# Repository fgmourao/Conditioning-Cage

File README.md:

# Conditioning Cage v2.0
** Under development

Hardware, firmware and desktop interface for classical fear conditioning.  
Arduino DUE stimulus generator controlled by a Python/PyQt5 application over USB.

---

## Origin

This project is a full rewrite of the system described in:

> Amaral Junior PA, Mourao FAG, Moraes MFD (2019).  
> *A Custom Microcontrolled and Wireless-Operated Chamber for Auditory Fear Conditioning.*  
> Frontiers in Neuroscience.  
> https://doi.org/10.3389/fnins.2019.01193

The original v1.0 architecture used an ESP8266 as a Wi-Fi master communicating with the Arduino DUE via SPI, with a browser-based HTML interface. Version 2.0 removes the ESP8266 entirely — a PyQt5 desktop application communicates directly with the DUE over its native USB port.

Beyond the architectural change, v2.0 introduces several new capabilities: adaptive DAC lookup tables for lower harmonic distortion across the full frequency range, an AM modulation channel with configurable modulator frequency, two independent programmable digital trigger outputs (pins 10 and 11) for synchronising external equipment, an OLED status display, a hardware watchdog with fault detection, and a calibration interface with per-bar shock selection.

---

## Changes from v1.0 to v2.0

### Architecture
The ESP8266 Wi-Fi master and SPI bus are removed entirely. Python communicates directly with the DUE over its native USB port using newline-terminated JSON. All stimulus timing is handled autonomously by the DUE after a single `start` command — no real-time control from the host is required during execution.

### Bug fixes and stability improvements

**Shock clock decoupled from DAC** — in v1.0 the shock interval counter (`iCountShockIntervals`) was incremented inside the `carrier()` ISR, which ran at the DAC rate. Changing `carrier_freq` silently altered shock pulse timing. In v2.0 the shock has its own dedicated Timer6 running at a fixed 10 kHz, completely independent of the DAC.

**Hardware ABORT pin pullup** — in v1.0 `pinABORT` was configured as `INPUT` with no pullup resistor, leaving the pin floating when the button was not pressed and susceptible to spurious aborts from electrical noise. In v2.0 it uses `INPUT_PULLUP`.

**DAC disabled between sounds** — in v1.0 `analogWrite(DAC1, 0)` at sound offset wrote zero but left the DAC channel enabled, injecting DC noise into the amplifier between trials. In v2.0 `dacc_disable_channel` is called at every sound offset and the coupling capacitor is pre-charged to midscale before each onset to eliminate transients.

**Shock pulse timing precision** — in v1.0 `floor()` was used to convert pulse times to tick counts, introducing a systematic downward truncation error. In v2.0 `roundf()` gives the nearest tick (0.1 ms resolution at 10 kHz).

**Watchdog** — v1.0 had no hardware fault detection. If Timer4 or Timer6 stalled, the experiment continued silently with no stimuli. In v2.0 a software watchdog monitors both timers; if either stops incrementing for 5 seconds a fault is declared, all outputs are driven LOW, and the Python interface displays a critical alert.

**DAC buffer type** — in v1.0 the DAC buffer was `uint32_t` (4 bytes per sample), wasting twice the RAM needed. In v2.0 it is `uint16_t` (2 bytes per sample), halving the buffer footprint to 2 KB.

### Sound generation

In v1.0 the carrier lookup table had a fixed 8 samples regardless of frequency. At low carrier frequencies (1–3 kHz) this produced visible harmonic distortion — only 8 points approximated each sine cycle. In v2.0 adaptive tables select 4, 8, 16, or 32 samples based on the carrier frequency, keeping the DAC update rate within the optimal range across the full 0–20 kHz span.

### New stimuli and features

- **LIGHT** — independent light stimulus (pin 45, square wave or DC HIGH) with its own onset, duration, and frequency per trial
- **Trigger 1 / Trigger 2** — two independent digital pulse outputs (pins 10 and 11) for synchronising external equipment, with configurable onset (s) and duration (ms) per trial
- **Baseline period** — quiet time before the first trial, separate from the inter-trial interval
- **Per-trial volume control** — sound amplitude programmable per trial (0–100%)
- **AM modulation** — configurable modulator frequency per trial; `modulator_freq = 0` gives a pure sine
- **OLED status display** — real-time trial state on an SSD1306 128×32 display
- **Bar selection** — calibration mode allows fixing a single shock bar for individual verification
- **Python desktop interface** — replaces the ESP8266 HTML page with a PyQt5 application featuring a trial timeline preview, protocol save/load, event log, and calibration dialogs

---

## Architecture

```
Python / PyQt5  (PC)
      │
      │  SerialUSB — native USB port (USB CDC)
      │
Arduino DUE
      ├─ DAC1         →  Sound  (AM sine, 0–20 kHz)
      ├─ Timer4/5     →  DAC clock / AM modulator ISR
      ├─ Timer6       →  Shock clock (10 kHz)
      ├─ Timer7       →  Light square wave
      ├─ Pins 23–37   →  Shock bars (8 outputs, round-robin)
      ├─ Pin 45       →  Light output
      ├─ Pin 46       →  Watchdog fault output
      ├─ Pin 48       →  Hardware ABORT input
      ├─ Pin 10        →  Trigger 1 output (digital pulse)
      ├─ Pin 11        →  Trigger 2 output (digital pulse)
      ├─ Pins 50–53   →  Sync outputs (SOUND, LIGHT, SHOCK, MOD)
      └─ Pins 20–21   →  I²C — OLED display (SDA / SCL)
```

The DUE stores the complete trial list in RAM and executes the experiment autonomously after a single `start` command. Python is responsible only for programming parameters, triggering execution, and monitoring status.

---

## Stimuli

Five independent stimuli with individual onset and duration per trial:

### Sound
- Output: DAC1 (12-bit, 0–3.3 V)
- Waveform: AM-modulated sine (`SINE_AM`) or pure sine
- Carrier: 0–20 kHz; modulator: 0–500 Hz
- Adaptive lookup tables (see [Sound generation](#sound-generation))
- AC coupling capacitor (10 µF) recommended in series on DAC1 output

### Light
- Output: pin 45, square wave 50% duty cycle
- Frequency: configurable; `light_freq = 9999` = DC HIGH (constant ON)

### Shock
- Outputs: pins 23, 25, 27, 29, 31, 33, 35, 37 (8 bars)
- Round-robin activation or fixed single bar (calibration)
- Pulse HIGH and LOW times configurable in ms (0.1 ms resolution at 10 kHz clock)

### Trigger 1 / Trigger 2
- Outputs: pin 10 (Trigger 1), pin 11 (Trigger 2)
- Simple digital HIGH pulse: onset in seconds, duration in milliseconds
- Independent of each other and of all other stimuli
- Intended for synchronising external equipment (cameras, stimulators, recording systems)

---

## Trial structure

Each trial stores 20 float parameters, transmitted semicolon-separated over serial:

| Field | Description | Unit |
|---|---|---|
| `baseline` | Quiet period before first trial | s |
| `silence` | Inter-trial interval | s |
| `onset_sound` | Sound onset within trial | s |
| `sound_duration` | Sound duration | s |
| `carrier_freq` | DAC carrier frequency; 0 = no sound | Hz |
| `modulator_freq` | AM modulator frequency; 0 = pure sine | Hz |
| `volume` | Sound amplitude | % |
| `waveform_type` | 0 = SINE_AM, 1 = SINE, 2 = SQUARE | — |
| `onset_shock` | Shock onset within trial | s |
| `shock_duration` | Shock duration; 0 = no shock | s |
| `pulse_high` | Shock bar ON time per pulse | ms |
| `pulse_low` | Shock bar OFF time between pulses | ms |
| `onset_light` | Light onset within trial | s |
| `light_duration` | Light duration; 0 = no light | s |
| `light_freq` | Light frequency; 9999 = DC HIGH | Hz |
| `bar_select` | 0 = round-robin, 1–8 = fixed bar | — |
| `onset_trig1` | Trigger 1 onset within trial; 0 = start of trial | s |
| `trig1_duration` | Trigger 1 pulse duration; 0 = disabled | ms |
| `onset_trig2` | Trigger 2 onset within trial; 0 = start of trial | s |
| `trig2_duration` | Trigger 2 pulse duration; 0 = disabled | ms |

---

## Serial protocol

All communication uses newline-terminated JSON objects:

```
{"cmd":"ping"}
    -> {"ok":true,"msg":"pong","version":"2.0"}

{"cmd":"program","n":N,"data":"f0;f1;..."}
    -> {"ok":true,"msg":"N trials programmed"}

{"cmd":"start"}
    -> {"ok":true,"msg":"started"}

{"cmd":"abort"}
    -> {"ok":true,"msg":"aborted"}

{"cmd":"status"}
    -> {"ok":true,"status":N,"trial":N,"total":N,
        "running":bool,"ready":bool,"fault":bool}
```

Status codes: `0` IDLE · `1` READY · `2` RUNNING · `3` DONE · `4` FAULT · `5` ABORTED

---

## Sync outputs

All sync pins are active HIGH while the corresponding stimulus is active.  
**Use these pins as the authoritative timing reference for external equipment** (electrophysiology, cameras). The `onset_*` fields in seconds carry a worst-case jitter of ~500 µs (one loop iteration); the sync pins do not.

| Pin | Signal | Description |
|---|---|---|
| 50 | SOUND_SYN | HIGH while sound is playing |
| 51 | LIGHT_SYN | HIGH while light is active |
| 52 | SHOCK_SYN | HIGH while shock is being delivered |
| 53 | MOD_SYN | Square wave at `modulator_freq`, phase-locked to AM envelope |

---

## OLED status display

Optional SSD1306 128×32 OLED on I²C (SDA = pin 20, SCL = pin 21, address 0x3C).  
Shows experiment state at each transition:

| State | Display |
|---|---|
| Startup | `Conditioning Cage / v2.0 Ready` |
| Trial onset | `TRIAL X/N` / `CS` · `CS + US` · `US` |
| Done | `Conditioning Cage / Done` |
| Aborted | `Conditioning Cage / Aborted` |

The firmware runs normally if the display is not connected.

---

## Sound generation

v2.0 uses adaptive lookup tables (`Waveforms.h`) to minimise harmonic distortion across the full frequency range:

| Carrier frequency | Table size | DAC update rate |
|---|---|---|
| > 10 000 Hz | 4 samples | up to 80 kHz |
| > 3 000 Hz | 8 samples | up to 80 kHz |
| > 1 000 Hz | 16 samples | up to 48 kHz |
| ≤ 1 000 Hz | 32 samples | up to 32 kHz |

All rates are within the SAM3X8E DAC hardware limit of 1 MHz.  
Buffer RAM cost: 32 × 32 × 2 bytes = 2 KB.

AM modulation uses a 32-sample unipolar envelope table. When `modulator_freq = 0` the carrier is output as a pure sine with no modulation.

---

## DAC signal conditioning

The DAC1 output is 0–3.3 V (unipolar). For audio output:

- Place a **10 µF electrolytic capacitor** in series (positive pole toward DAC1) to block DC and pass the AC signal
- Place a **10 kΩ resistor** between the amplifier input and GND to anchor the input when the DAC is disabled
- Use a **potentiometer (10–50 kΩ)** between the capacitor and the amplifier input for level control
- Connect the cable shield to GND on the DUE side only (single-end grounding prevents ground loops)

The firmware disables DAC1 between sounds (`dacc_disable_channel`) and pre-charges the coupling capacitor to midscale before each trial onset to prevent transients.

---

## Python application

### Requirements

```
pip install pyserial PyQt5
```

Python 3.8 or later.

### Features

- Dark/Light-theme PyQt5 desktop application
- Trial configuration panel: per-stimulus onset, duration, frequency, volume, pulse timing, trigger durations
- Recorded trials table with per-row delete
- Timeline preview: block diagram of all trials on a shared time axis with a real-time progress line during execution; rows are shown only for stimuli with non-zero duration
- Event log with timestamps (`YYYY-MM-DD HH:MM:SS`) — exportable via Save Log
- **Protocol menu:** Save Protocol, Load Protocol, Clear All Trials, Save Log
- **Calibration menu:** Sound, Light, Shock — continuous single-trial stimulus stopped by ABORT; shock calibration allows bar selection and configurable pulse timing
- **Help menu:** Info dialog
- Port selector with refresh button
- 4-second timeout warning if DUE does not respond after connection
- Firmware version check on connect (warns if not v2.0)
- Watchdog fault popup with critical alert
- Hardware ABORT button (pin 48) is read inside the trial timing loop and during inter-trial silences — responsive at any point during experiment execution

### Poll strategy

The poll timer (`{"cmd":"status"}` every 1500 ms) is stopped when the experiment starts to prevent USB interrupt collisions with Timer4 on the Native Port. One poll is scheduled at the calculated onset of each trial using `QTimer.singleShot`. A generation counter invalidates scheduled polls that remain pending after an ABORT. The poll timer resumes when the experiment ends or is aborted.

---

## Hardware requirements

| Component | Specification |
|---|---|
| Microcontroller | Arduino DUE |
| USB connection | Native port (second USB connector) |
| Shock bars | 8 outputs — pins 23, 25, 27, 29, 31, 33, 35, 37 |
| Light output | Pin 45 |
| Trigger 1 output | Pin 10 — digital pulse |
| Trigger 2 output | Pin 11 — digital pulse |
| ABORT button | Momentary switch — pin 48 to GND |
| DAC coupling | 10 µF electrolytic capacitor in series on DAC1 |
| Amplifier | Class-D module (e.g. TDA8932); 10–50 kΩ potentiometer at input |
| Speaker | Tweeter (2–20 kHz); 4 Ω or 8 Ω |
| OLED (optional) | SSD1306 128×32, I²C, address 0x3C |

---

## Files

| File | Description |
|---|---|
| `cage_app_dark.py` | Main application — dark theme |
| `Stimuli_PY_DUE.ino` | Arduino DUE firmware |
| `Waveforms.h` | Adaptive DAC lookup tables |
| `image.png` | Logo displayed in the application header |

Arduino library dependencies (install via Arduino IDE Library Manager):
- **DueTimer** (Ivan Seidel)
- **Adafruit GFX Library**
- **Adafruit SSD1306**

---

## Known limitations

- Noise waveforms (white, pink) are not implemented. The lookup-table architecture is periodic; a possible approach is to generate noise buffers in Python (NumPy/SciPy) and send them as custom tables over serial.
- If the USB cable is disconnected during an experiment, the DUE continues executing autonomously. The only way to stop it is the hardware ABORT button (pin 48).

---

## License

Documentation licensed under Creative Commons Attribution-NonCommercial 4.0 International (CC BY-NC 4.0).

---

## Authors

**v1.0 (2019)**  
Paulo Aparecido Amaral Junior, Flavio Afonso Goncalves Mourao, Marcio Flavio Dutra Moraes  
*Núcleo de Neurociências, Federal University of Minas Gerais, Brazil*

**v2.0 (2026)**  
Flavio Afonso Goncalves Mourao — [mourao.fg@gmail.com](mailto:mourao.fg@gmail.com)  
*CNPq/MCTI/FNDCT Nº 21/2024 — Processo 446467/2024-3*  
*Federal University of Minas Gerais, Brazil*

---

*Last update: April 2026*

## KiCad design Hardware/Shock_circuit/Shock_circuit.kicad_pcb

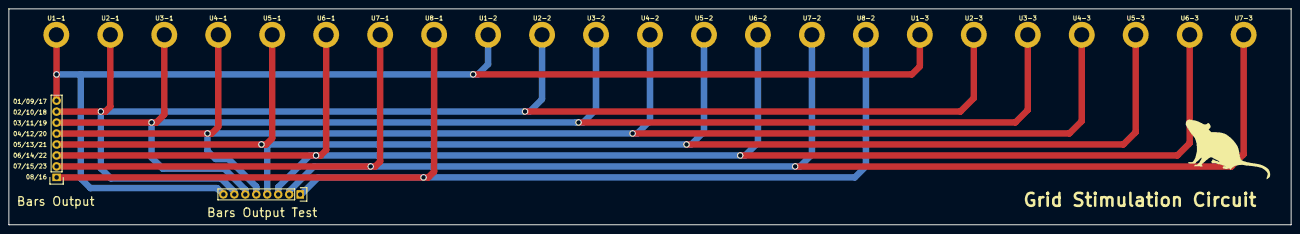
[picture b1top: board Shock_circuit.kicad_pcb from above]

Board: 2 copper layers, 297.0 x 50.0 mm, 25 parts (0 on the bottom side), 8 nets.

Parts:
P1: Bars Output Test; Pin_Header_Straight_1x08
P2: Bars Output; Pin_Header_Straight_1x08
U1-1, U1-2, U1-3, U2-1, U2-2, U2-3, U3-1, U3-2, U3-3, U4-1, U4-2, U4-3, U5-1, U5-2, U5-3, U6-1, U6-2, U6-3, U7-1, U7-2, U7-3, U8-1, U8-2: Bar_Hole

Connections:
/InBarra1: P1.8, P2.8, U1-1.1, U1-2.1, U1-3.1
/InBarra2: P1.7, P2.7, U2-1.1, U2-2.1, U2-3.1
/InBarra3: P1.6, P2.6, U3-1.1, U3-2.1, U3-3.1
/InBarra4: P1.5, P2.5, U4-1.1, U4-2.1, U4-3.1
/InBarra5: P1.4, P2.4, U5-1.1, U5-2.1, U5-3.1
/InBarra6: P1.3, P2.3, U6-1.1, U6-2.1, U6-3.1
/InBarra7: P1.2, P2.2, U7-1.1, U7-2.1, U7-3.1
/InBarra8: P1.1, P2.1, U8-1.1, U8-2.1

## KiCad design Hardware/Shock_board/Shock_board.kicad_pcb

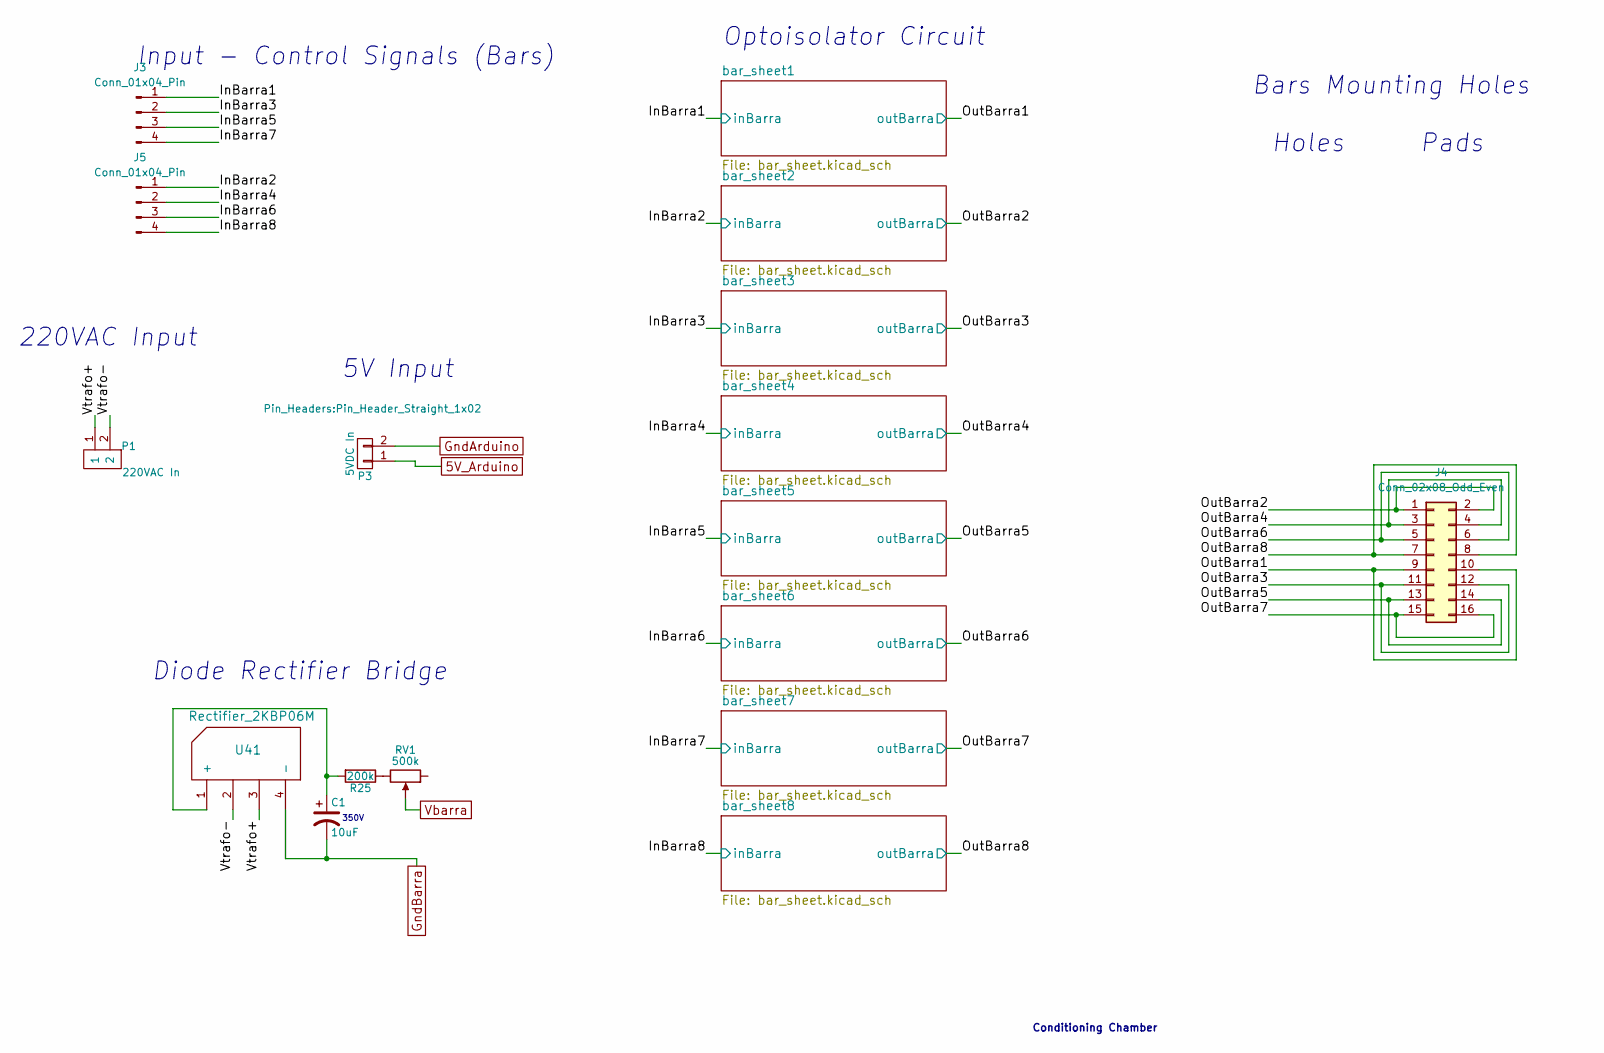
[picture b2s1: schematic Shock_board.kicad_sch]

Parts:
C1: 10uF; CP_Radial_D10.0mm_P7.50mm
J3: Conn_01x04_Pin; PinHeader_1x04_P2.54mm_Vertical
J4: Conn_02x08_Odd_Even; IDC-Header_2x08_P2.54mm_Vertical
J5: Conn_01x04_Pin; PinSocket_1x04_P2.54mm_Vertical
P1: 220VAC In; Pin_Header_Straight_1x02_Pitch2.54mm
P3: 5VDC In; Pin_Header_Straight_1x02
R25: 200k; R_Axial_DIN0207_L6.3mm_D2.5mm_P10.16mm_Horizontal
RV1: 500k; Potentiometer_Alps_RK163_Single_Vertical
U41: Rectifier_2KBP06M

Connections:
5V_Arduino: P3.1; also elsewhere on the board
/Vtrafo+: P1.1, U41.3
/Vtrafo-: P1.2, U41.2
GndArduino: P3.2; also elsewhere on the board
GndBarra: C1.2, U41.4 (-); also elsewhere on the board
unnamed: J4.1, J4.2
unnamed: J4.3, J4.4
unnamed: J4.5, J4.6
unnamed: J4.7, J4.8
unnamed: J4.9, J4.10
unnamed: J4.11, J4.12
unnamed: J4.13, J4.14
unnamed: J4.15, J4.16
unnamed 53: R25.1, RV1.3; also elsewhere on the board
unnamed: C1.1, R25.2, U41.1 (+)

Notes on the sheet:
350V
Input - Control Signals (Bars)
Diode Rectifier Bridge
220VAC Input
Bars Mounting Holes
Optoisolator Circuit
5V Input
Holes
Conditioning Chamber
Pads

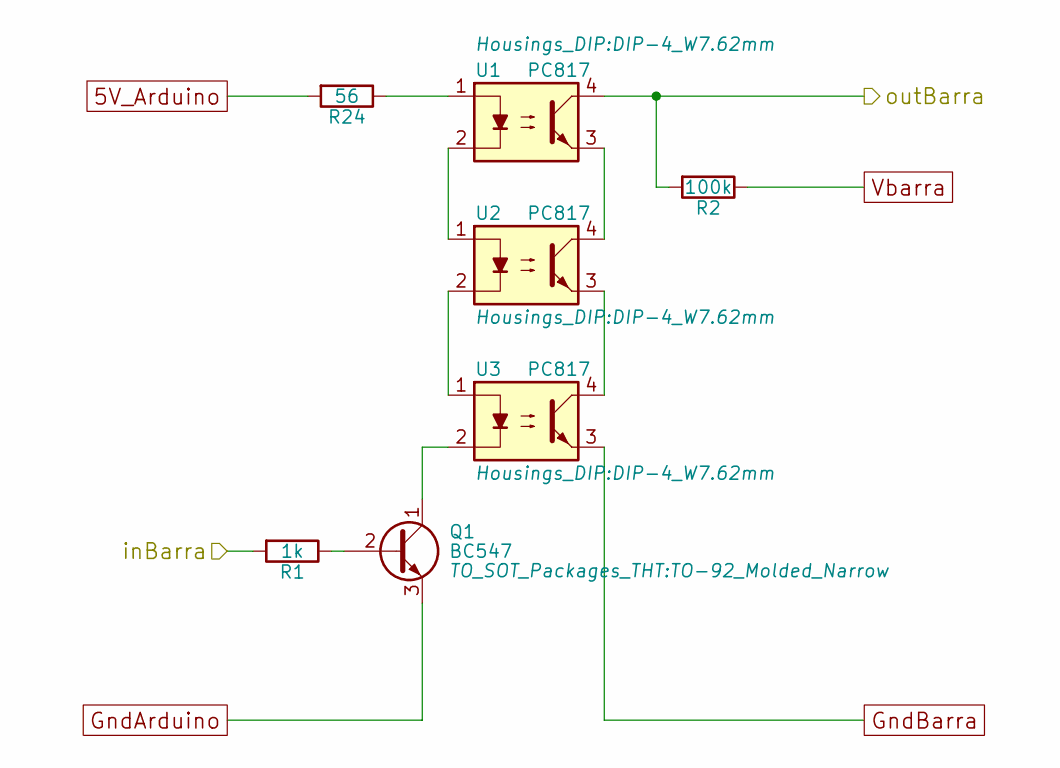
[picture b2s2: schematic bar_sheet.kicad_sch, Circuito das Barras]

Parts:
Q1: BC547; TO-92_Molded_Narrow
R1: 1k; R_Axial_DIN0207_L6.3mm_D2.5mm_P10.16mm_Horizontal
R2: 100k; R_Axial_DIN0411_L9.9mm_D3.6mm_P5.08mm_Vertical
R24: 56; R_Axial_DIN0207_L6.3mm_D2.5mm_P10.16mm_Horizontal
U1, U2, U3: PC817; DIP-4_W7.62mm

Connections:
5V_Arduino: R24.2; also elsewhere on the board
/InBarra1: R1.2; also elsewhere on the board
/OutBarra1: R2.2, U1.4; also elsewhere on the board
GndArduino: Q1.3 (E); also elsewhere on the board
GndBarra: U3.3; also elsewhere on the board
unnamed: Q1.2 (B), R1.1
unnamed: Q1.1 (C), U3.2
unnamed: R24.1, U1.1
unnamed: U1.2, U2.1
unnamed: U1.3, U2.4
unnamed: U2.2, U3.1
unnamed: U2.3, U3.4
Vbarra: R2.1; also elsewhere on the board

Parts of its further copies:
Q2, Q3, Q4, Q5, Q6, Q7, Q8: BC547; TO-92_Molded_Narrow
R3, R5, R7, R9, R11, R13, R15: 1k; R_Axial_DIN0207_L6.3mm_D2.5mm_P10.16mm_Horizontal
R4, R6, R8, R10, R12, R14, R16: 100k; R_Axial_DIN0411_L9.9mm_D3.6mm_P5.08mm_Vertical
R17, R18, R19, R20, R21, R22, R23: 56; R_Axial_DIN0207_L6.3mm_D2.5mm_P10.16mm_Horizontal
U4, U5, U6, U7, U8, U9, U10, U11, U12, U13, U14, U15, U16, U17, U18, U19, U20, U21, U22, U23, U24: PC817; DIP-4_W7.62mm

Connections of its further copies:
5V_Arduino: R17.2, R18.2, R19.2, R20.2, R21.2, R22.2, R23.2; also elsewhere on the board
/InBarra2: R3.2; also elsewhere on the board
/InBarra3: R5.2; also elsewhere on the board
/InBarra4: R7.2; also elsewhere on the board
/InBarra5: R9.2; also elsewhere on the board
/InBarra6: R11.2; also elsewhere on the board
/InBarra7: R13.2; also elsewhere on the board
/InBarra8: R15.2; also elsewhere on the board
/OutBarra2: R4.2, U4.4; also elsewhere on the board
/OutBarra3: R6.2, U7.4; also elsewhere on the board
/OutBarra4: R8.2, U10.4; also elsewhere on the board
/OutBarra5: R10.2, U13.4; also elsewhere on the board
/OutBarra6: R12.2, U16.4; also elsewhere on the board
/OutBarra7: R14.2, U19.4; also elsewhere on the board
/OutBarra8: R16.2, U22.4; also elsewhere on the board
GndArduino: Q2.3 (E), Q3.3 (E), Q4.3 (E), Q5.3 (E), Q6.3 (E), Q7.3 (E), Q8.3 (E); also elsewhere on the board
GndBarra: U6.3, U9.3, U12.3, U15.3, U18.3, U21.3, U24.3; also elsewhere on the board
unnamed: Q2.2 (B), R3.1
unnamed: Q2.1 (C), U6.2
unnamed: Q3.2 (B), R5.1
unnamed: Q3.1 (C), U9.2
unnamed: Q4.2 (B), R7.1
unnamed: Q4.1 (C), U12.2
unnamed: Q5.2 (B), R9.1
unnamed: Q5.1 (C), U15.2
unnamed: Q6.2 (B), R11.1
unnamed: Q6.1 (C), U18.2
unnamed: Q7.2 (B), R13.1
unnamed: Q7.1 (C), U21.2
unnamed: Q8.2 (B), R15.1
unnamed: Q8.1 (C), U24.2
unnamed: R17.1, U7.1
unnamed: R18.1, U10.1
unnamed: R19.1, U13.1
unnamed: R20.1, U16.1
unnamed: R21.1, U19.1
unnamed: R22.1, U22.1
unnamed: R23.1, U4.1
unnamed: U4.2, U5.1
unnamed: U4.3, U5.4
unnamed: U5.2, U6.1
unnamed: U5.3, U6.4
unnamed: U7.2, U8.1
unnamed: U7.3, U8.4
unnamed: U8.2, U9.1
unnamed: U8.3, U9.4
unnamed: U10.2, U11.1
unnamed: U10.3, U11.4
unnamed: U11.2, U12.1
unnamed: U11.3, U12.4
unnamed: U13.2, U14.1
unnamed: U13.3, U14.4
unnamed: U14.2, U15.1
unnamed: U14.3, U15.4
unnamed: U16.2, U17.1
unnamed: U16.3, U17.4
unnamed: U17.2, U18.1
unnamed: U17.3, U18.4
unnamed: U19.2, U20.1
unnamed: U19.3, U20.4
unnamed: U20.2, U21.1
unnamed: U20.3, U21.4
unnamed: U22.2, U23.1
unnamed: U22.3, U23.4
unnamed: U23.2, U24.1
unnamed: U23.3, U24.4
Vbarra: R4.1, R6.1, R8.1, R10.1, R12.1, R14.1, R16.1; also elsewhere on the board

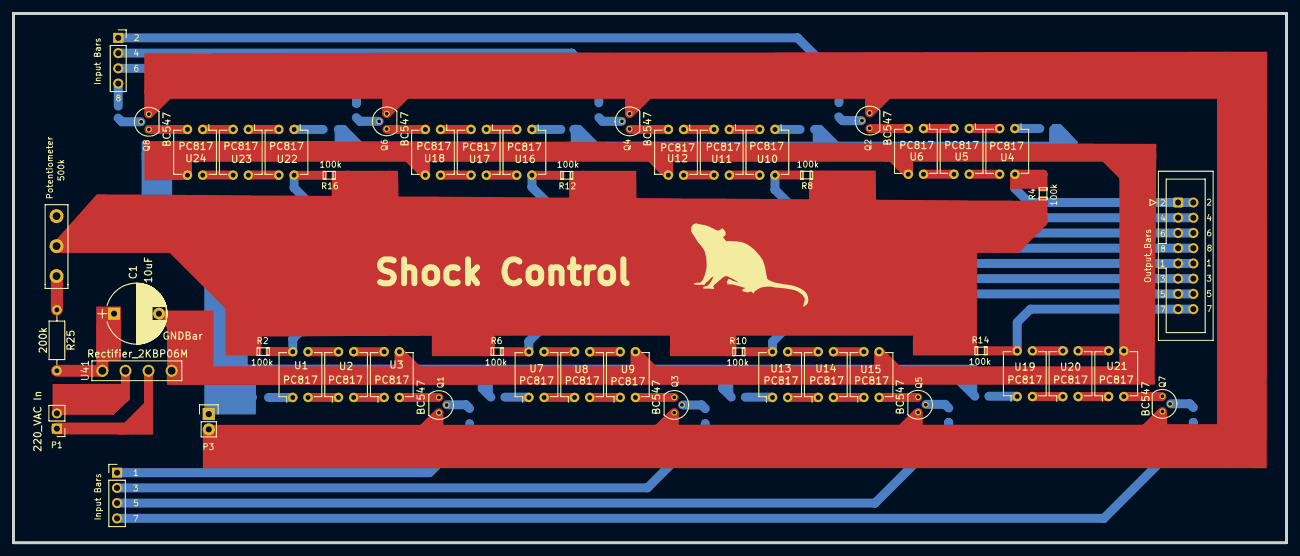
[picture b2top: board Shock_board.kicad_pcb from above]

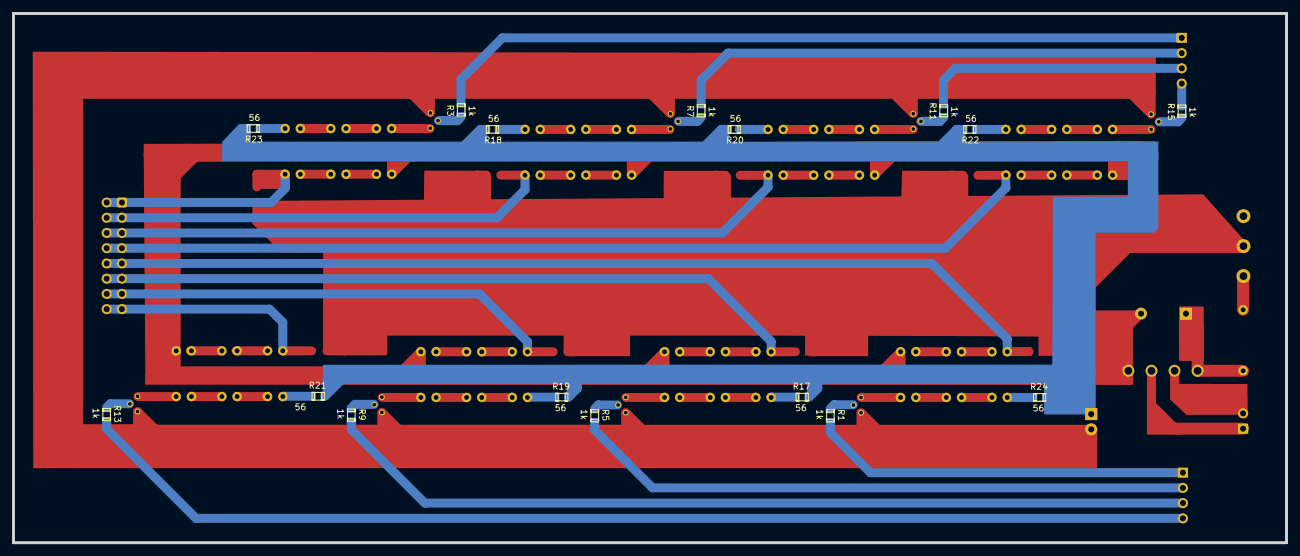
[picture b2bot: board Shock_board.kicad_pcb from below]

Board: 2 copper layers, 212.3 x 88.3 mm, 65 parts (16 on the bottom side), 80 nets.

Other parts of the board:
Input Bars: PinHeader_1x04_P2.54mm_Vertical
Input Bars#2: PinSocket_1x04_P2.54mm_Vertical
Output_Bars: IDC-Header_2x08_P2.54mm_Vertical
Potentiometer: 500k; Potentiometer_Alps_RK163_Single_Vertical

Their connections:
/InBarra1: Input Bars.1; also elsewhere on the board
/InBarra2: Input Bars#2.1; also elsewhere on the board
/InBarra3: Input Bars.2; also elsewhere on the board
/InBarra4: Input Bars#2.2; also elsewhere on the board
/InBarra5: Input Bars.3; also elsewhere on the board
/InBarra6: Input Bars#2.3; also elsewhere on the board
/InBarra7: Input Bars.4; also elsewhere on the board
/InBarra8: Input Bars#2.4; also elsewhere on the board
/OutBarra1: Output_Bars.9, Output_Bars.10; also elsewhere on the board
/OutBarra2: Output_Bars.1, Output_Bars.2; also elsewhere on the board
/OutBarra3: Output_Bars.11, Output_Bars.12; also elsewhere on the board
/OutBarra4: Output_Bars.3, Output_Bars.4; also elsewhere on the board
/OutBarra5: Output_Bars.13, Output_Bars.14; also elsewhere on the board
/OutBarra6: Output_Bars.5, Output_Bars.6; also elsewhere on the board
/OutBarra7: Output_Bars.15, Output_Bars.16; also elsewhere on the board
/OutBarra8: Output_Bars.7, Output_Bars.8; also elsewhere on the board
unnamed 53: Potentiometer.3; also elsewhere on the board
Vbarra: Potentiometer.2; also elsewhere on the board

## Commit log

2026-04-13 Update April 2026
2026-04-14 update serial timer
2026-04-14 Add HTML tooltips
    - Introduce `TOOLTIP_DOCS` dictionary containing rich text (HTML) descriptions for all experimental parameters.
    - Modify `make_input_row` to return the `QLabel` instance alongside the row and input widgets to allow direct tooltip binding.
    - Implement `apply_tooltips()` to map centralized documentation to their respective label and input field pairs.
    - Inject global `QToolTip` CSS rules into `QApplication.instance()` to ensure correct rendering and visibility within the application's top-level context.
    - Update `_build_left_panel` to correctly unpack the modified `make_input_row` return values.
2026-04-14 Update April 14, 2026
2026-04-19 Update April 18,2026
2026-04-28 update - Apr 28 2026
